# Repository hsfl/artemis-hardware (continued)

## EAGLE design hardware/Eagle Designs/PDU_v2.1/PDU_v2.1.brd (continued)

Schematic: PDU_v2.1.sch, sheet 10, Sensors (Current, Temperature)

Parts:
C8, C29, C30, C37, C42, C61, C68, C69, C70, C71: 0.1 uF; 0805
C82: 0.1 uF; 0603-CAP
R26, R34, R36, R52, R54, R64, R65, R67, R76, R78: 3.3 k; 0805
R35, R39, R63, R66, R79, R80, R81, R84, R85, R88: 10; 0805
R53, R77, R87, R89, R90: 2 m; 0805
R61: 45.3 k; 0603-RES
R62: 10 k; 0603-RES
U15, U30, U31, U32, U33: INA219BIDR; SOIC127P599X175-8N
U18: TMP36FSZ; R_8_ADI

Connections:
AIN1: R61.1, R62.2; also elsewhere on the board
BUS_3V3: C8.1, C68.1, C69.1, C70.1, C71.1, C82.2, R26.1, R34.1, R36.1, R52.1, R54.1, R64.1, R65.1, R67.1, R76.1, R78.1, U15.1 (A1), U15.5 (VS), U18.5 (!SHUTDOWN), U18.8 (+VS), U30.5 (VS), U31.2 (A0), U31.5 (VS), U32.5 (VS), U33.5 (VS); also elsewhere on the board
CS_SOL1_VIN+: C30.1, R63.1, U30.8 (VIN+)
CS_SOL1_VIN-: C30.2, R66.1, U30.7 (VIN-)
CS_SOL2_VIN+: C37.1, R79.1, U31.8 (VIN+)
CS_SOL2_VIN-: C37.2, R80.1, U31.7 (VIN-)
CS_SOL3_VIN+: C42.1, R81.1, U32.8 (VIN+)
CS_SOL3_VIN-: C42.2, R88.1, U32.7 (VIN-)
CS_SOL4_VIN+: C61.1, R84.1, U33.8 (VIN+)
CS_SOL4_VIN-: C61.2, R85.1, U33.7 (VIN-)
CS_VBATT: R35.2, R53.2; also elsewhere on the board
CS_VBATT_VIN+: C29.1, R35.1, U15.8 (VIN+)
CS_VBATT_VIN-: C29.2, R39.1, U15.7 (VIN-)
GND: C8.2, C68.2, C69.2, C70.2, C71.2, C82.1, R62.1, U15.2 (A0), U15.6 (GND), U18.4 (GND), U30.1 (A1), U30.2 (A0), U30.6 (GND), U31.1 (A1), U31.6 (GND), U32.1 (A1), U32.6 (GND), U33.1 (A1), U33.6 (GND); also elsewhere on the board
I2C1_SCL: R36.2, R54.2, R64.2, R67.2, R78.2, U15.4 (SCL), U30.4 (SCL), U31.4 (SCL), U32.4 (SCL), U33.2 (A0), U33.4 (SCL); also elsewhere on the board
I2C1_SDA: R26.2, R34.2, R52.2, R65.2, R76.2, U15.3 (SDA), U30.3 (SDA), U31.3 (SDA), U32.2 (A0), U32.3 (SDA), U33.3 (SDA); also elsewhere on the board
unnamed: R61.2, U18.1 (VOUT)
SOLAR_IN1: R63.2, R77.2; also elsewhere on the board
SOLAR_IN1_LOAD: R66.2, R77.1; also elsewhere on the board
SOLAR_IN2: R79.2, R87.2; also elsewhere on the board
SOLAR_IN2_LOAD: R80.2, R87.1; also elsewhere on the board
SOLAR_IN3: R81.2, R89.2; also elsewhere on the board
SOLAR_IN3_LOAD: R88.2, R89.1; also elsewhere on the board
SOLAR_IN4: R84.2, R90.2; also elsewhere on the board
SOLAR_IN4_LOAD: R85.2, R90.1; also elsewhere on the board
VBATT: R39.2, R53.1; also elsewhere on the board

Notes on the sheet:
All cap/res in current sensor circuit is 0805 size.
All cap/res in temp sensor is 0603 size.
Analog Temperature Sensor
Current Sensor (VBATT)
Current Sensor (Solar Panels)

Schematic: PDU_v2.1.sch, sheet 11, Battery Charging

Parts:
C10, C12, C18, C91: 0.1 uF; 0805
C14, C39: 10 uF; 0805
C38: 4.7 uF; 0805
C40, C41: 1 uF; 0805
D1: CMDSH-3TR; SOD2512X110N
D3, D5: MBR230S1F; CR_0LSFT1G_ONS
D6, D7, D8, D9, D10, D11, D12: PMEG10020ELRX; CFP3_SOD123W_NEX
D13: LED_0805
J18: 5037630491; CON_5037630491
L2: AIML-0805-150K-T; AIML-0805_ABR
R27: 3 k; 0805
R28: 6.04 k; 0805
R29: 0; 0805
R37: 26.7 k; 0805
R55: 169 k; 0805
R56: 28.4k; 0603-RES
R91, R95: 1; 0805
R92, R94: 3.01 k; 0805
R96: 5.1 k; 0805
U20: LTC4012IUFPBF; QFN50P400X400X80-21N
U28: SI4431BDY-T1-E3; SOIC-8_SI
U29: AO4818B; SOIC8_NARROW_VIS

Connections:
5V_USB_CHRG: D12.2 (12); also elsewhere on the board
BATT_CHRG: C39.1, D5.1, R94.2, R95.1, U20.11 (BAT); also elsewhere on the board
BGATE: U20.16 (BGATE), U29.4 (2)
CHRG: D13.2, U20.7 (~CHRG); also elsewhere on the board
GND: C14.2, C38.2, C39.2, C40.2, C41.2, C91.2, J18.2, J18.4, J18.5, J18.6, R28.1, R37.1, R56.1, U20.21 (GND); also elsewhere on the board
INFET: U20.3 (INFET), U28.4 (G)
INH_SW1_COM: D6.1 (11), D7.1 (11), D8.1 (11), D9.1 (11), D10.1 (11), D11.1 (11), D12.1 (11), J18.1
INH_SW1_NC: C91.1, J18.3, R27.2, U20.4 (DCIN), U28.5 (D_2), U28.6 (D_3), U28.7 (D_4), U28.8 (D)
ITH: C10.1, U20.12 (ITH)
unnamed: D13.1, R27.1
unnamed: C10.2, R28.2
unnamed: C12.2, R96.1, U20.1 (CLN)
unnamed: R29.1, U20.20 (BOOST)
unnamed: C40.1, C41.1, D1.A, U20.17 (INTVDD)
unnamed: C18.1, D1.C, R29.2
unnamed: R92.1, U20.15 (CSP)
unnamed: R94.1, U20.14 (CSN)
unnamed: C38.1, R37.2, U20.13 (PROG)
unnamed: R55.1, U20.10 (FBDIV)
unnamed: R55.2, R56.2, U20.9 (VFB)
R_SENSE_R_IN1: L2.1, R92.2, R95.2
S2: D3.1, U29.2 (1)
SHDN: U20.6 (~SHDN); also elsewhere on the board
SOLAR_IN1_LOAD: D6.2 (12); also elsewhere on the board
SOLAR_IN2_LOAD: D7.2 (12); also elsewhere on the board
SOLAR_IN3_LOAD: D8.2 (12); also elsewhere on the board
SOLAR_IN4_LOAD: D9.2 (12); also elsewhere on the board
SOLAR_IN5_LOAD: D10.2 (12)
SOLAR_IN6_LOAD: D11.2 (12)
SW: C18.2, D3.2, L2.2, U20.18 (SW), U29.3, U29.6 (8), U29.7
TGATE: U20.19 (TGATE), U29.1 (4)
U2_S: C12.1, R91.1, U20.2 (CLP), U28.1 (S_2), U28.2 (S_3), U28.3 (S)
VBATT: C14.1, D5.2, R91.2, R96.2, U29.5 (6), U29.8 (5); also elsewhere on the board

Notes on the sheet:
All cap/res are 0603 size unless indicated otherwise.
Battery Charger Controller
Solar Cell Inhibit Switch Connectors
(From) Solar Panel Connectors
0805
~ACP left floating when unused (pg. 8)
*use AIML-0805-100K-T for 10 uH (0805) *use AIML-0805-150K-T for 15 uH (0805)
*From MCU
*To MCU
*Power to System Specifically, VBATT supplies PDU
Signal generated from MCU into LTC4012's Pin => *From MCU Signal generated from LTC4012's Pin into MCU => *To MCU
RC Circuit
BATT_CHRG is supplied by Batteries on PyCubed Battery Board
INH_SW1_NC = "SOLAR_VCC" Solar Input connected to Solar Cell Inhibit Switch
Two 1 uF Cap in Parallel = 2 uF Tot Cap
0603
~ICL left floating when unused (pg. 8)
(RIN1)
(RIN2)
(RSENSE)
LED (BATT CHRG)

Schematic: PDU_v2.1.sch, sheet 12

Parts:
J15: 5037630291; CON_5037630291
NT1: AIMC-0805-2N2S-T; INDC2012X105N
R82, R83: 1 M; 0805
U10, U24: AO3404A; SOT-23-3L_AOS

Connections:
GND: J15.3, J15.4, NT1.1; also elsewhere on the board
unnamed: R82.1, U10.3 (D), U24.1 (G)
POST_RBF_VBATT: U24.2 (S); also elsewhere on the board
PY_VBATT: J15.1, R82.2, U24.3 (D); also elsewhere on the board
RBF_GND: NT1.2, R83.2, U10.2 (S)
RBF_SW: J15.2, R83.1, U10.1 (G)

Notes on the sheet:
0805
Functionality: Pin Removed = Open Circuit = PDU Powered On Pin In = Closed Circuit = PDU Powered Off
Remove Before Flight (RBF) Circuit
PY_VBATT: Power source directly from PyCubed Battery Board (Pre-RBF Circuit) POST_RBF_VBATT: Power source that gets (noise) filtered (Post-RBF Circuit)
Male Connector (MC) External Part Not Shown MC in (Pin In) MC disconnected (Pin Out)

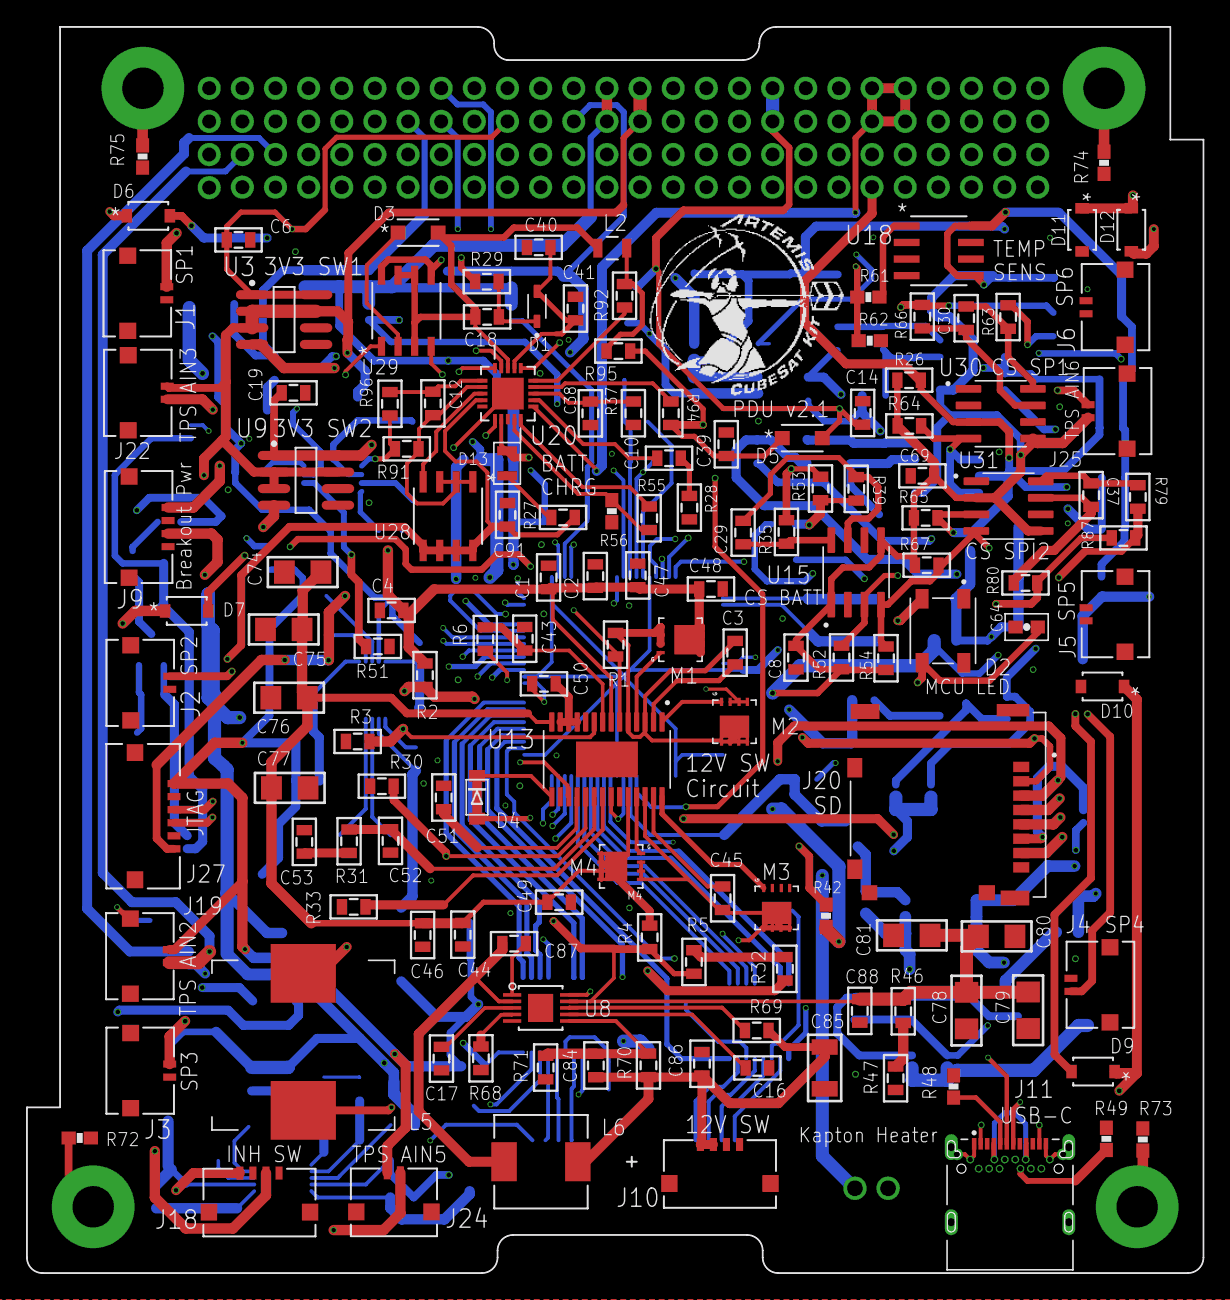
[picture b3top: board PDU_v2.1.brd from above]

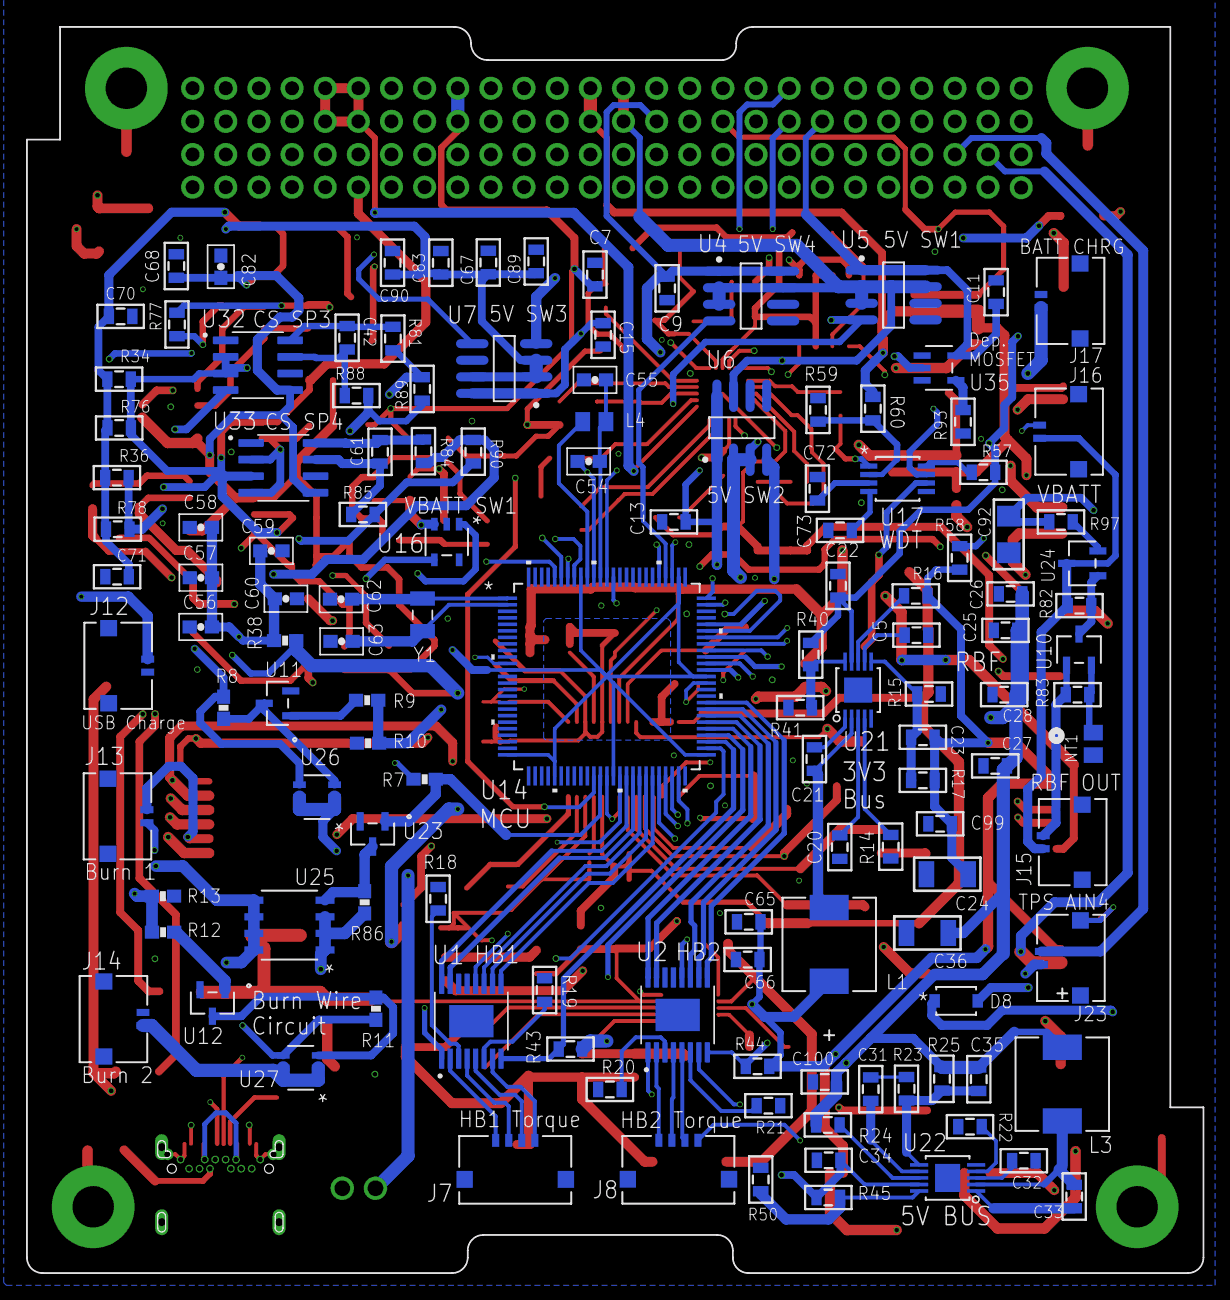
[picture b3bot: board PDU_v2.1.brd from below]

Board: 4 copper layers, 90.2 x 95.5 mm, 275 parts (130 on the bottom side), 190 nets.

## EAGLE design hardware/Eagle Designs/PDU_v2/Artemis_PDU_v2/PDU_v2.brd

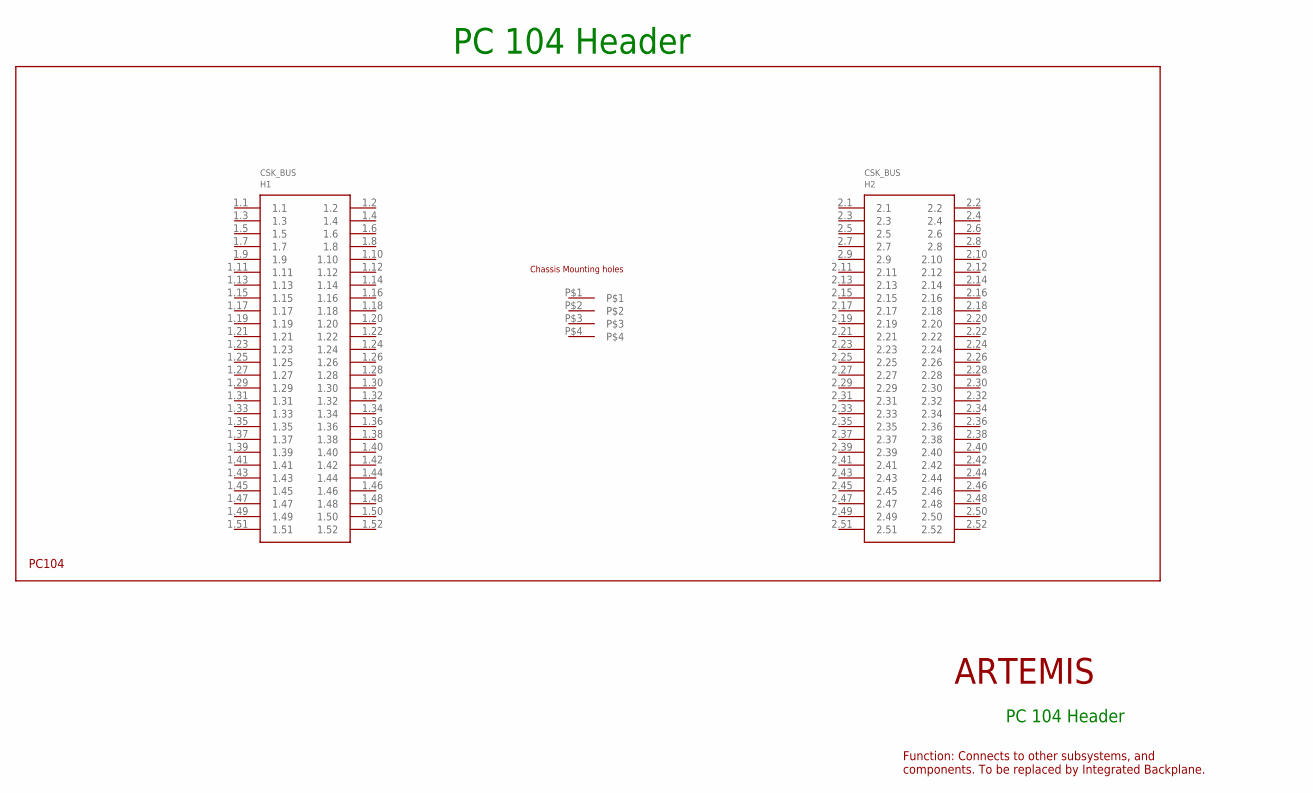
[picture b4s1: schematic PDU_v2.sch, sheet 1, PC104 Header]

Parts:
H1: PC104_WCONN

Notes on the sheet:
PC 104 Header
ARTEMIS
Function: Connects to other subsystems, and components. To be replaced by Integrated Backplane.

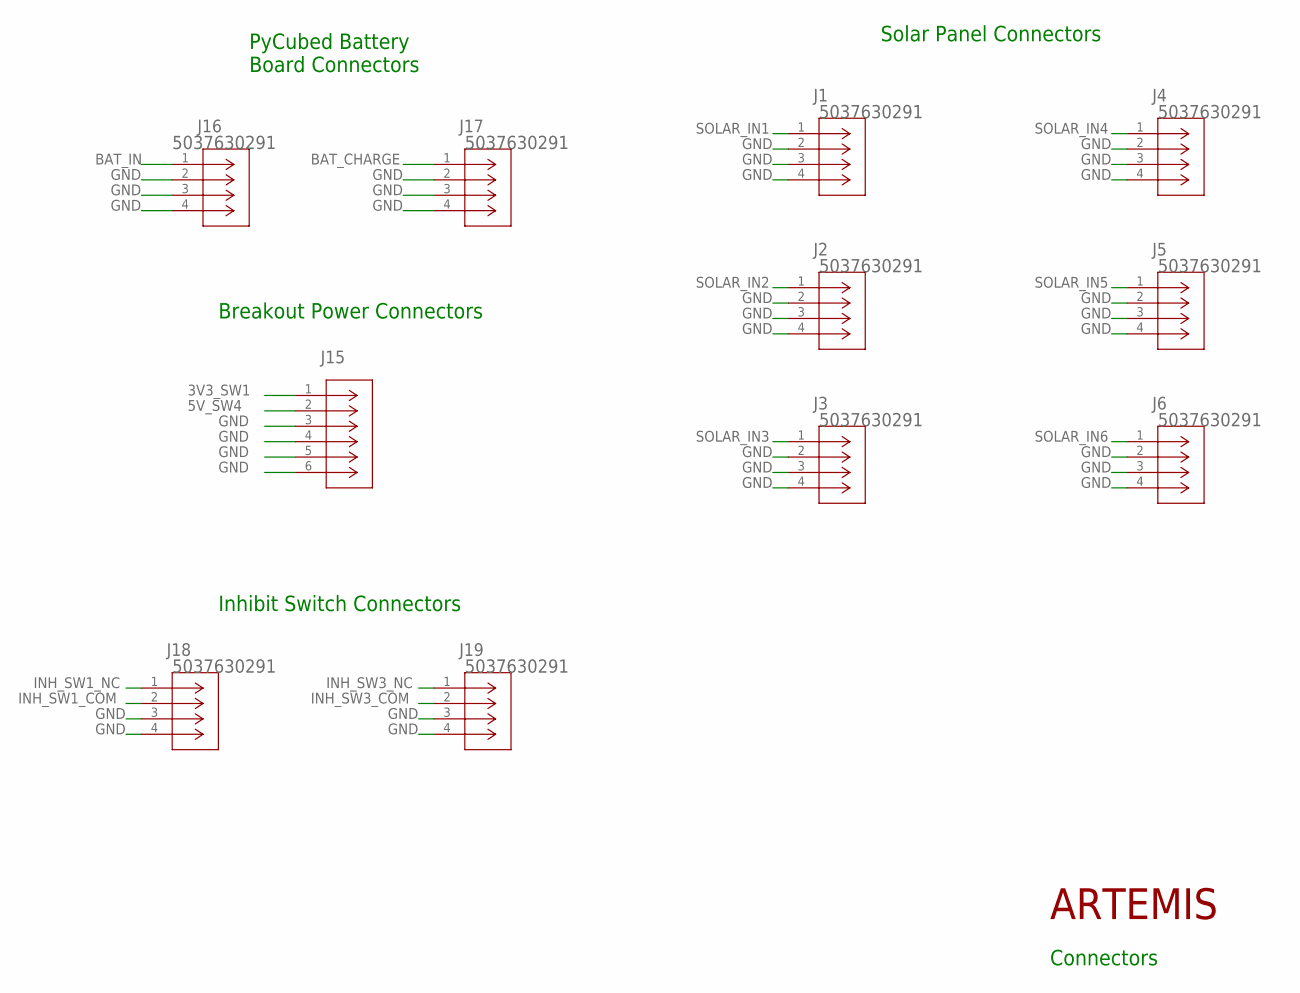
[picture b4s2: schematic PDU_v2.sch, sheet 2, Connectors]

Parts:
J1, J2, J3, J4, J5, J6, J16, J17, J18, J19: 5037630291; CON_5037630291
J15: 5037630491; CON_5037630491

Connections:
3V3_SW1: J15.1
5V_SW4: J15.2
BAT_CHARGE: J17.1
BAT_IN: J16.1
GND: J1.2, J1.3, J1.4, J2.2, J2.3, J2.4, J3.2, J3.3, J3.4, J4.2, J4.3, J4.4, J5.2, J5.3, J5.4, J6.2, J6.3, J6.4, J15.3, J15.4, J15.5, J15.6, J16.2, J16.3, J16.4, J17.2, J17.3, J17.4, J18.3, J18.4, J19.3, J19.4; also elsewhere on the board
INH_SW1_COM: J18.2
INH_SW1_NC: J18.1
INH_SW3_COM: J19.2
INH_SW3_NC: J19.1
SOLAR_IN1: J1.1; also elsewhere on the board
SOLAR_IN2: J2.1; also elsewhere on the board
SOLAR_IN3: J3.1; also elsewhere on the board
SOLAR_IN4: J4.1; also elsewhere on the board
SOLAR_IN5: J5.1; also elsewhere on the board
SOLAR_IN6: J6.1; also elsewhere on the board

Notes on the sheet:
ARTEMIS
Solar Panel Connectors
PyCubed Battery Board Connectors
Breakout Power Connectors
Inhibit Switch Connectors
Connectors

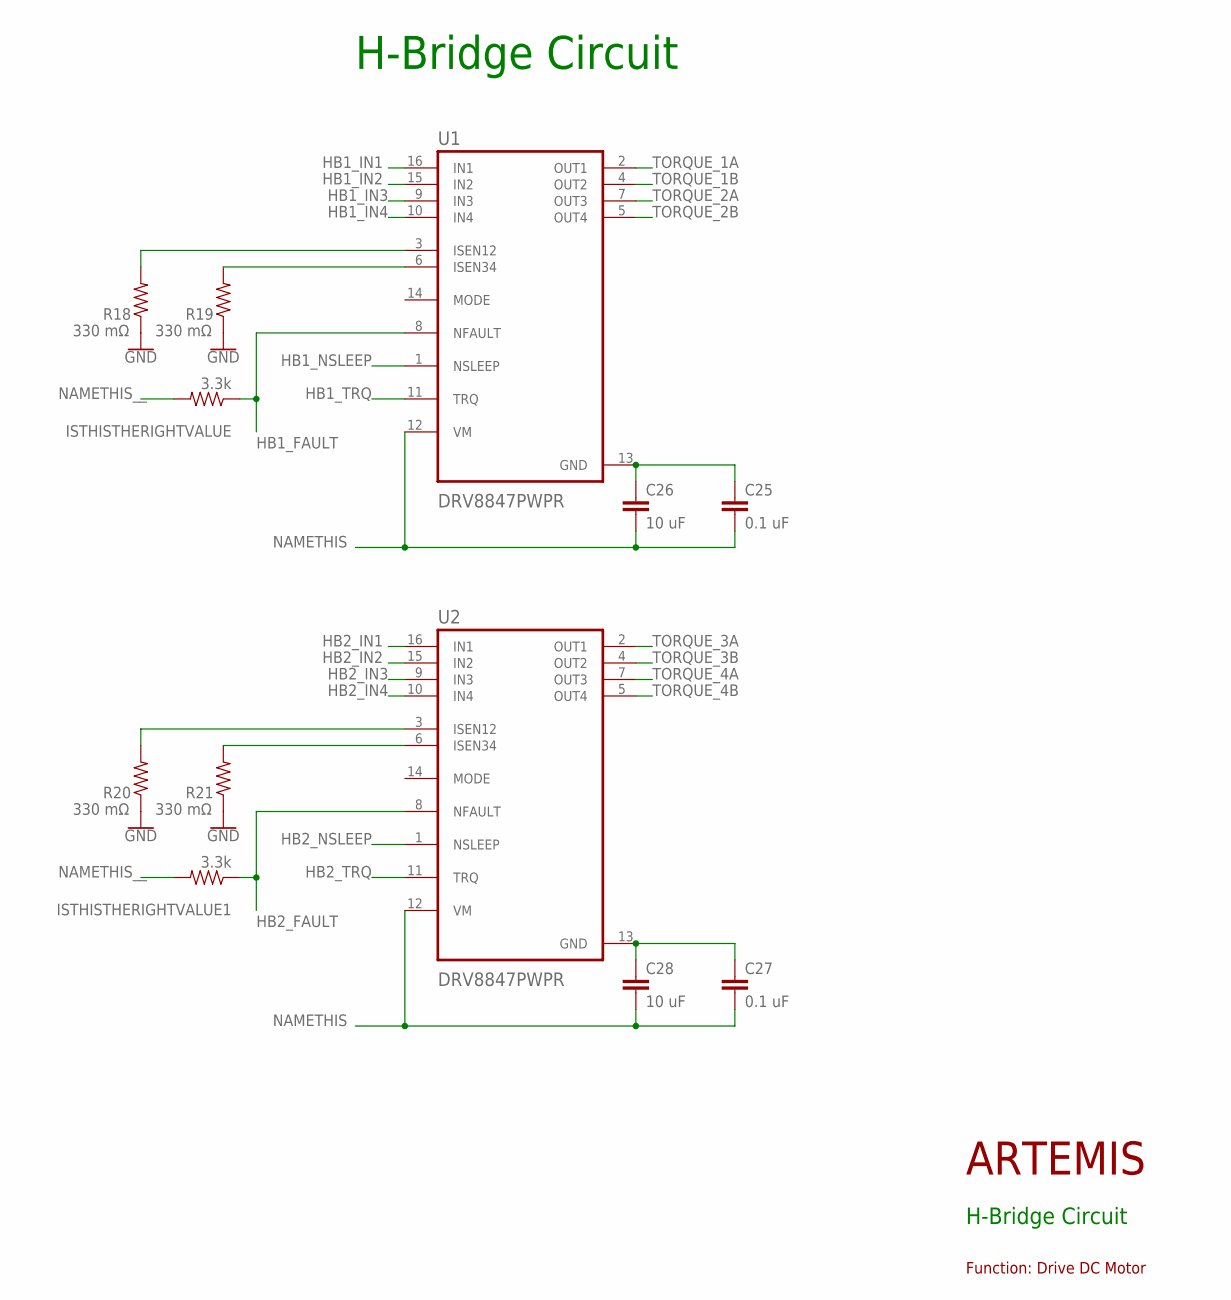
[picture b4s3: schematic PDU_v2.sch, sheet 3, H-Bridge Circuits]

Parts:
C25, C27: 0.1 uF; 0805
C26, C28: 10 uF; 0805
ISTHISTHERIGHTVALUE, ISTHISTHERIGHTVALUE1: 3.3k; 0805
R18, R19, R20, R21: 330 mΩ; 0805
U1, U2: DRV8847PWPR; SOP65P640X120-17N

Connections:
GND: R18.1, R19.1, R20.1, R21.1; also elsewhere on the board
HB1_FAULT: ISTHISTHERIGHTVALUE.1, U1.8 (NFAULT)
HB1_IN1: U1.16 (IN1)
HB1_IN2: U1.15 (IN2)
HB1_IN3: U1.9 (IN3)
HB1_IN4: U1.10 (IN4)
HB1_NSLEEP: U1.1 (NSLEEP)
HB1_TRQ: U1.11 (TRQ)
HB2_FAULT: ISTHISTHERIGHTVALUE1.1, U2.8 (NFAULT)
HB2_IN1: U2.16 (IN1)
HB2_IN2: U2.15 (IN2)
HB2_IN3: U2.9 (IN3)
HB2_IN4: U2.10 (IN4)
HB2_NSLEEP: U2.1 (NSLEEP)
HB2_TRQ: U2.11 (TRQ)
unnamed: C27.1, C28.1, U2.13 (GND)
unnamed: C25.1, C26.1, U1.13 (GND)
unnamed: R19.2, U1.6 (ISEN34)
unnamed: R18.2, U1.3 (ISEN12)
unnamed: R21.2, U2.6 (ISEN34)
unnamed: R20.2, U2.3 (ISEN12)
NAMETHIS: C25.2, C26.2, C27.2, C28.2, U1.12 (VM), U2.12 (VM)
NAMETHIS__: ISTHISTHERIGHTVALUE.2, ISTHISTHERIGHTVALUE1.2
TORQUE_1A: U1.2 (OUT1)
TORQUE_1B: U1.4 (OUT2)
TORQUE_2A: U1.7 (OUT3)
TORQUE_2B: U1.5 (OUT4)
TORQUE_3A: U2.2 (OUT1)
TORQUE_3B: U2.4 (OUT2)
TORQUE_4A: U2.7 (OUT3)
TORQUE_4B: U2.5 (OUT4)

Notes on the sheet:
H-Bridge Circuit
Function: Drive DC Motor
ARTEMIS

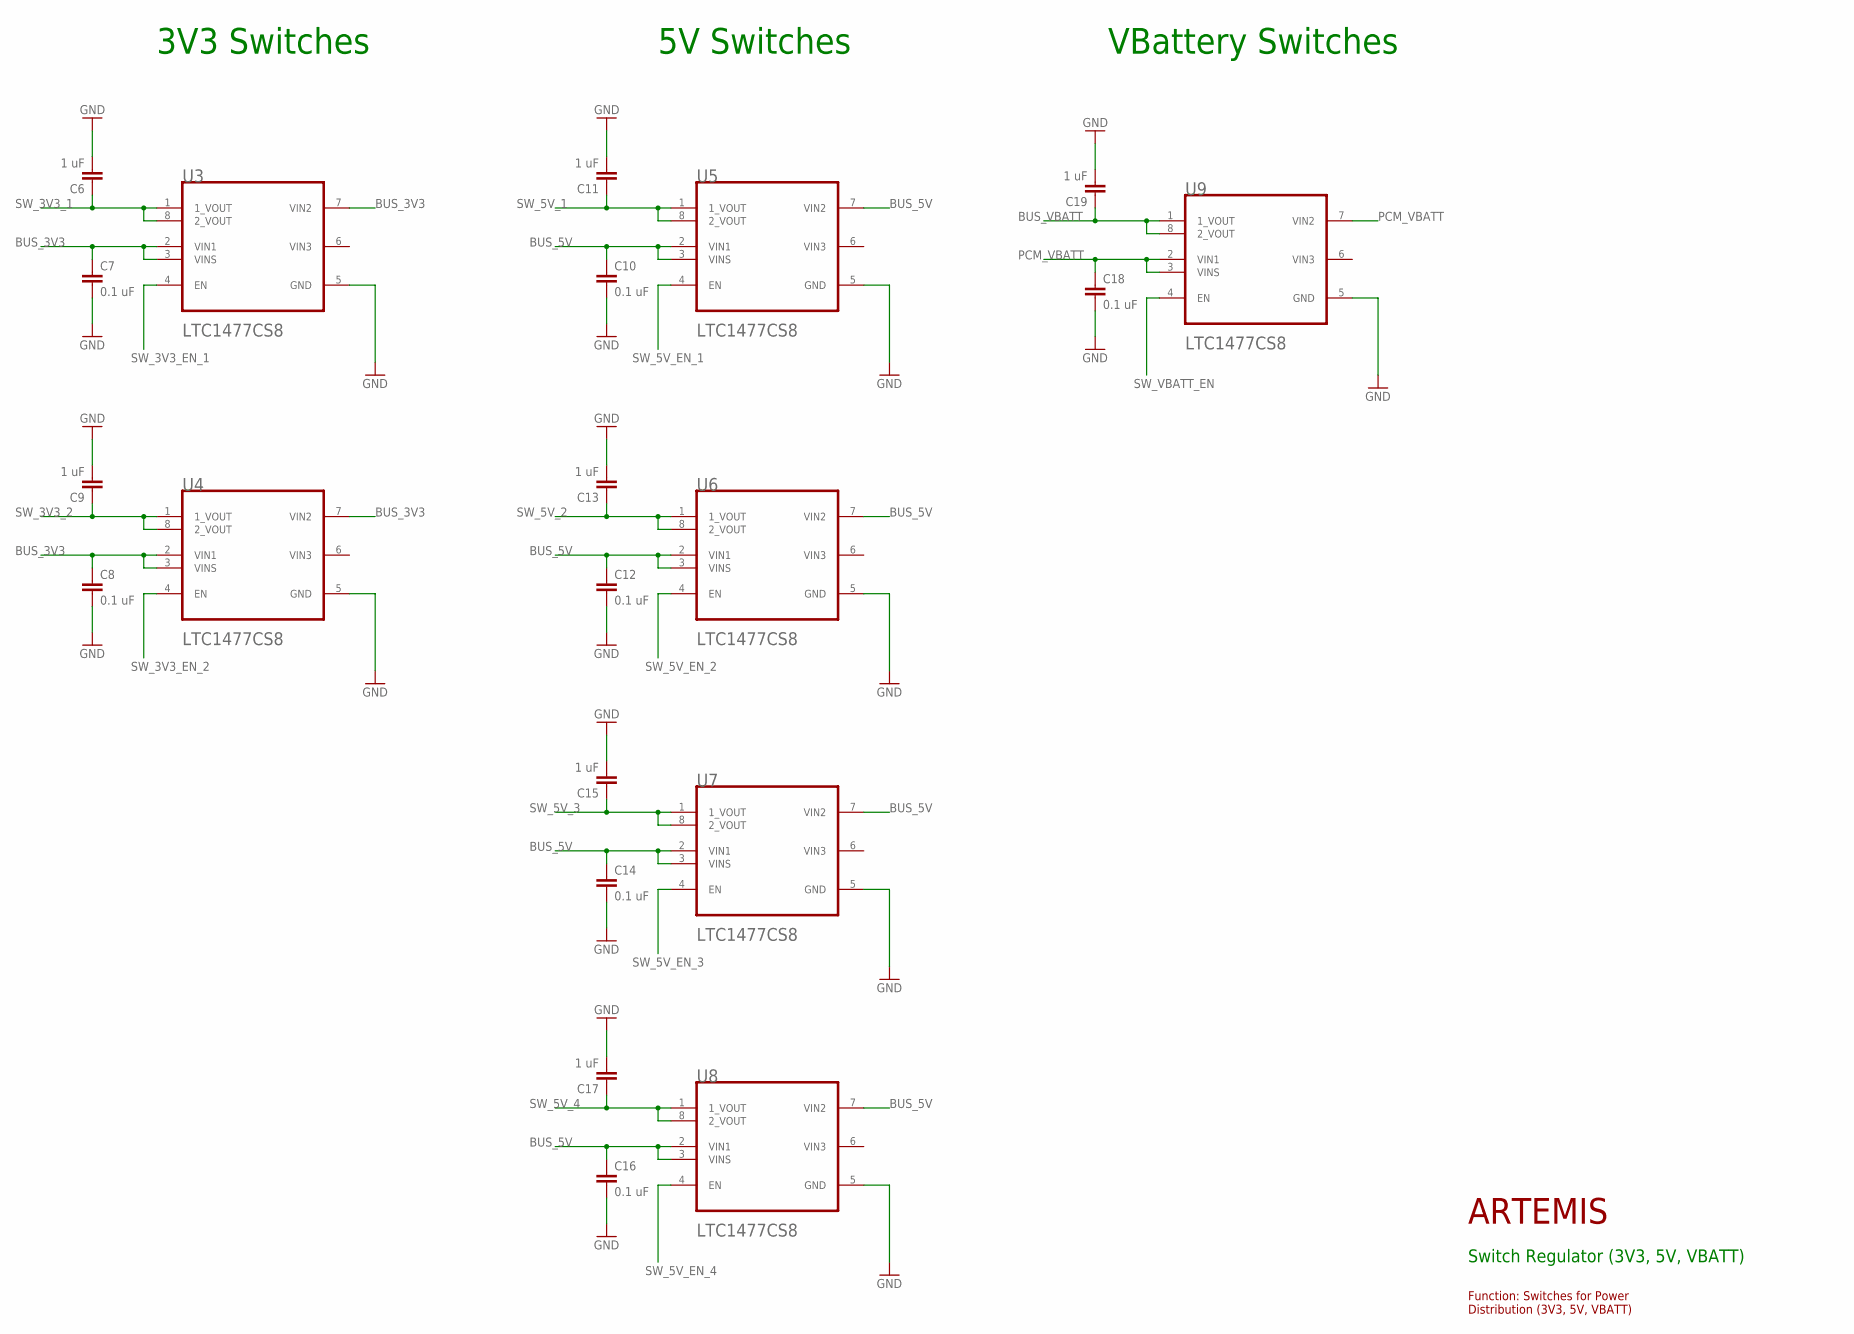
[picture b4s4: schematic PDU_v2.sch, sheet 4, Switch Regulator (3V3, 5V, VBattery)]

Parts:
C6, C9, C11, C13, C15, C17, C19: 1 uF; 0805
C7, C8, C10, C12, C14, C16, C18: 0.1 uF; 0805
U3, U4, U5, U6, U7, U8, U9: LTC1477CS8LINEAR_TECHNOLOGY_LTC1477CS8_0_2; LINEAR_TECHNOLOGY_LTC1477CS8_2

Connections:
BUS_3V3: C7.1, C8.1, U3.2 (VIN1), U3.3 (VINS), U3.7 (VIN2), U4.2 (VIN1), U4.3 (VINS), U4.7 (VIN2); also elsewhere on the board
BUS_5V: C10.1, C12.1, C14.1, C16.1, U5.2 (VIN1), U5.3 (VINS), U5.7 (VIN2), U6.2 (VIN1), U6.3 (VINS), U6.7 (VIN2), U7.2 (VIN1), U7.3 (VINS), U7.7 (VIN2), U8.2 (VIN1), U8.3 (VINS), U8.7 (VIN2); also elsewhere on the board
BUS_VBATT: C19.1, U9.1 (1_VOUT), U9.8 (2_VOUT)
GND: C6.2, C7.2, C8.2, C9.2, C10.2, C11.2, C12.2, C13.2, C14.2, C15.2, C16.2, C17.2, C18.2, C19.2, U3.5 (GND), U4.5 (GND), U5.5 (GND), U6.5 (GND), U7.5 (GND), U8.5 (GND), U9.5 (GND); also elsewhere on the board
PCM_VBATT: C18.1, U9.2 (VIN1), U9.3 (VINS), U9.7 (VIN2); also elsewhere on the board
SW_3V3_1: C6.1, U3.1 (1_VOUT), U3.8 (2_VOUT)
SW_3V3_2: C9.1, U4.1 (1_VOUT), U4.8 (2_VOUT)
SW_3V3_EN_1: U3.4 (EN)
SW_3V3_EN_2: U4.4 (EN)
SW_5V_1: C11.1, U5.1 (1_VOUT), U5.8 (2_VOUT)
SW_5V_2: C13.1, U6.1 (1_VOUT), U6.8 (2_VOUT)
SW_5V_3: C15.1, U7.1 (1_VOUT), U7.8 (2_VOUT)
SW_5V_4: C17.1, U8.1 (1_VOUT), U8.8 (2_VOUT)
SW_5V_EN_1: U5.4 (EN)
SW_5V_EN_2: U6.4 (EN)
SW_5V_EN_3: U7.4 (EN)
SW_5V_EN_4: U8.4 (EN)
SW_VBATT_EN: U9.4 (EN)
VIN3: U3.6 (VIN3), U4.6 (VIN3), U5.6 (VIN3), U6.6 (VIN3), U7.6 (VIN3), U8.6 (VIN3), U9.6 (VIN3)

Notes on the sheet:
3V3 Switches
5V Switches
VBattery Switches
Function: Switches for Power Distribution (3V3, 5V, VBATT)
ARTEMIS
Switch Regulator (3V3, 5V, VBATT)

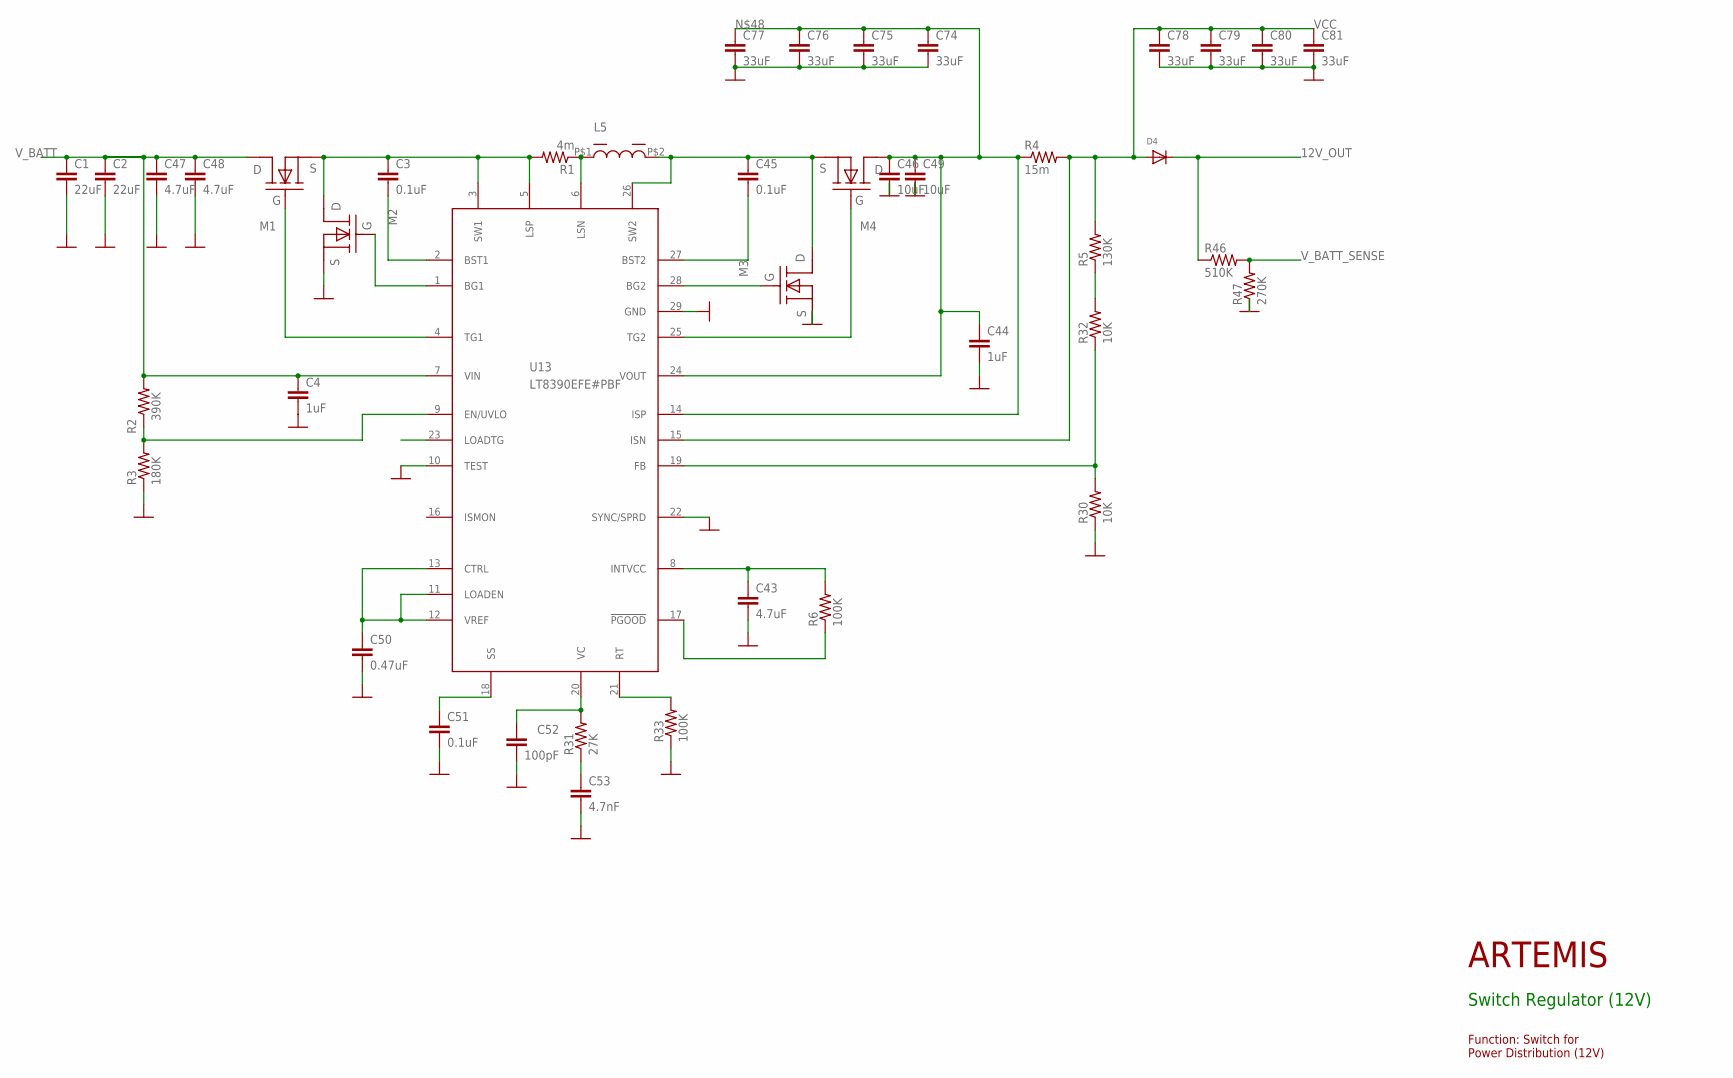
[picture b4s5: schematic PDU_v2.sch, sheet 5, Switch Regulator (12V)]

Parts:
C1, C2: 22uF; 0805
C3, C45, C51: 0.1uF; 0805
C4, C44: 1uF; 0805
C43, C47, C48: 4.7uF; 0805
C46, C49: 10uF; 0805
C50: 0.47uF; 0805
C52: 100pF; 0805
C53: 4.7nF; 0805
C74, C75, C76, C77, C78, C79, C80, C81: 33uF; 1206
D4: DIODE_SOD-123FL; SOD-123FL
L5: 6uH; 7443551600
M1, M2: BSZ100N06LS3
M3, M4: BSZ033NE2LS5; BSZ100N06LS3
R1: 4m; 0805
R2: 390K; 0805
R3: 180K; 0805
R4: 15m; 0805
R5: 130K; 0805
R6, R33: 100K; 0805
R30, R32: 10K; 0805
R31: 27K; 0805
R46: 510K; 0805
R47: 270K; 0805
U13: LT8390EFE#PBF; SOP65P640X120-29N

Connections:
12V_OUT: D4.C, R46.1
GND: C1.2, C2.2, C4.2, C43.2, C44.2, C46.2, C47.2, C48.2, C49.2, C50.2, C51.2, C52.2, C53.2, C74.2, C75.2, C76.2, C77.2, C78.2, C79.2, C80.2, C81.2, M2.P$2 (S), M2.P$3 (S), M2.P$4 (S), M3.P$2 (S), M3.P$3 (S), M3.P$4 (S), R3.1, R30.1, R33.1, R47.1, U13.10 (TEST), U13.22 (SYNC/SPRD), U13.29 (GND); also elsewhere on the board
unnamed: C3.1, M1.P$2 (S), M1.P$3 (S), M1.P$4 (S), M2.P$5 (D), M2.P$6 (D), M2.P$7 (D), M2.P$8 (D), M2.P$9 (D), R1.2, U13.3 (SW1), U13.5 (LSP)
unnamed: C3.2, U13.2 (BST1)
unnamed: M2.P$1 (G), U13.1 (BG1)
unnamed: M1.P$1 (G), U13.4 (TG1)
unnamed: R2.1, R3.2, U13.9 (EN/UVLO)
unnamed: M3.P$1 (G), U13.28 (BG2)
unnamed: C52.1, R31.2, U13.20 (VC)
unnamed: C50.1, U13.11 (LOADEN), U13.12 (VREF), U13.13 (CTRL)
unnamed: R5.1, R32.2
unnamed: C45.1, L5.P$2, M3.P$5 (D), M3.P$6 (D), M3.P$7 (D), M3.P$8 (D), M3.P$9 (D), M4.P$2 (S), M4.P$3 (S), M4.P$4 (S), U13.26 (SW2)
unnamed: R6.1, U13.17 (!PGOOD)
unnamed: C43.1, R6.2, U13.8 (INTVCC)
unnamed: L5.P$1, R1.1, U13.6 (LSN)
unnamed: C45.2, U13.27 (BST2)
unnamed: C44.1, C46.1, C49.1, C74.1, C75.1, C76.1, C77.1, M4.P$5 (D), M4.P$6 (D), M4.P$7 (D), M4.P$8 (D), M4.P$9 (D), R4.1, U13.14 (ISP), U13.24 (VOUT)
unnamed: M4.P$1 (G), U13.25 (TG2)
unnamed: C51.1, U13.18 (SS)
unnamed: R30.2, R32.1, U13.19 (FB)
unnamed: R33.2, U13.21 (RT)
unnamed: C53.1, R31.1
VCC: C78.1, C79.1, C80.1, C81.1, D4.A, R4.2, R5.2, U13.15 (ISN); also elsewhere on the board
V_BATT: C1.1, C2.1, C4.1, C47.1, C48.1, M1.P$5 (D), M1.P$6 (D), M1.P$7 (D), M1.P$8 (D), M1.P$9 (D), R2.2, U13.7 (VIN)
V_BATT_SENSE: R46.2, R47.2

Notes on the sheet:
Function: Switch for Power Distribution (12V)
ARTEMIS
Switch Regulator (12V)

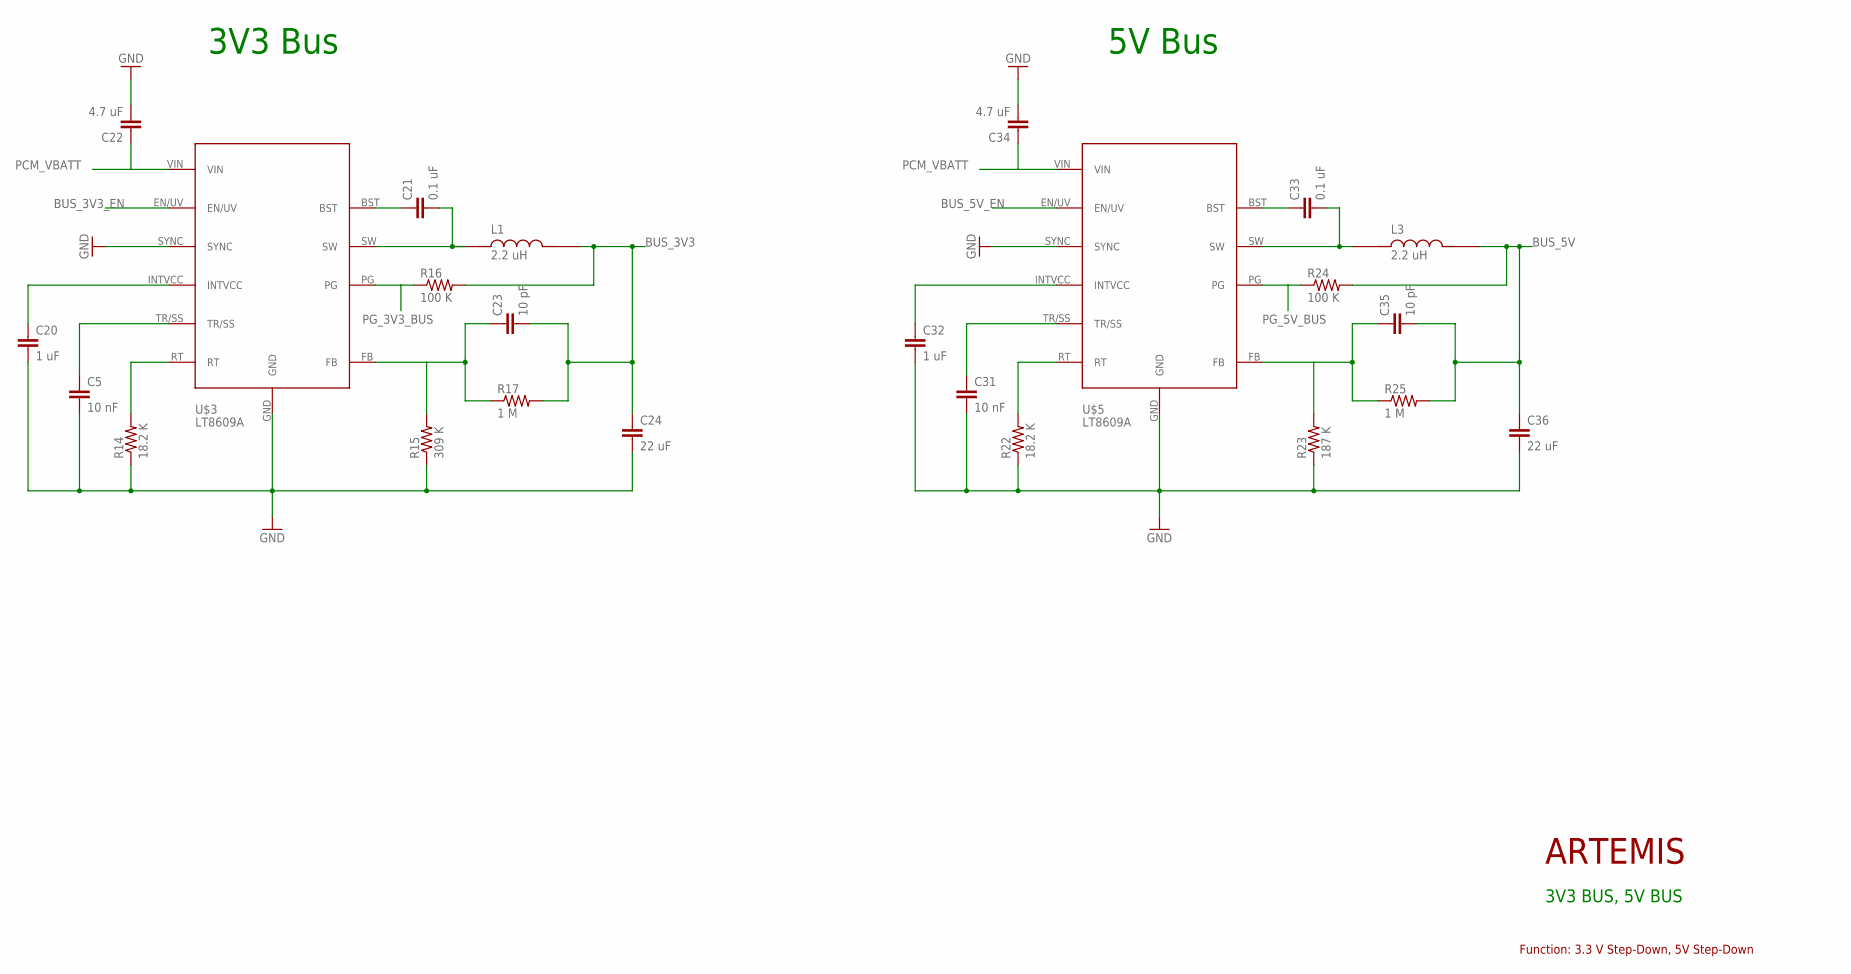
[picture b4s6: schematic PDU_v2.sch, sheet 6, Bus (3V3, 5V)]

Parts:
C5, C31: 10 nF; 0805
C20, C32: 1 uF; 0805
C21, C33: 0.1 uF; 0805
C22, C34: 4.7 uF; 0805
C23, C35: 10 pF; 0805
C24, C36: 22 uF; 1206
L1, L3: 2.2 uH; IND_XFL4020-222ME
R14, R22: 18.2 K; 0805
R15: 309 K; 0805
R16, R24: 100 K; 0805
R17, R25: 1 M; 0805
R23: 187 K; 0805
U$3, U$5: LT8609A; MSOP_10PAD

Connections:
BUS_3V3: C23.2, C24.1, L1.2, R16.2, R17.2; also elsewhere on the board
BUS_3V3_EN: U$3.EN/UV
BUS_5V: C35.2, C36.1, L3.2, R24.2, R25.2; also elsewhere on the board
BUS_5V_EN: U$5.EN/UV
GND: C5.2, C20.2, C22.2, C24.2, C31.2, C32.2, C34.2, C36.2, R14.1, R15.1, R22.1, R23.1, U$3.GND, U$3.SYNC, U$5.GND, U$5.SYNC; also elsewhere on the board
unnamed: C20.1, U$3.INTVCC
unnamed: R14.2, U$3.RT
unnamed: C23.1, R15.2, R17.1, U$3.FB
unnamed: C5.1, U$3.TR/SS
unnamed: C21.1, U$3.BST
unnamed: C21.2, L1.1, U$3.SW
unnamed: R22.2, U$5.RT
unnamed: C31.1, U$5.TR/SS
unnamed: C32.1, U$5.INTVCC
unnamed: C33.1, U$5.BST
unnamed: C33.2, L3.1, U$5.SW
unnamed: C35.1, R23.2, R25.1, U$5.FB
PCM_VBATT: C22.1, C34.1, U$3.VIN, U$5.VIN; also elsewhere on the board
PG_3V3_BUS: R16.1, U$3.PG
PG_5V_BUS: R24.1, U$5.PG

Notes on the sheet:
3V3 Bus
ARTEMIS
5V Bus
3V3 BUS, 5V BUS
Function: 3.3 V Step-Down, 5V Step-Down
